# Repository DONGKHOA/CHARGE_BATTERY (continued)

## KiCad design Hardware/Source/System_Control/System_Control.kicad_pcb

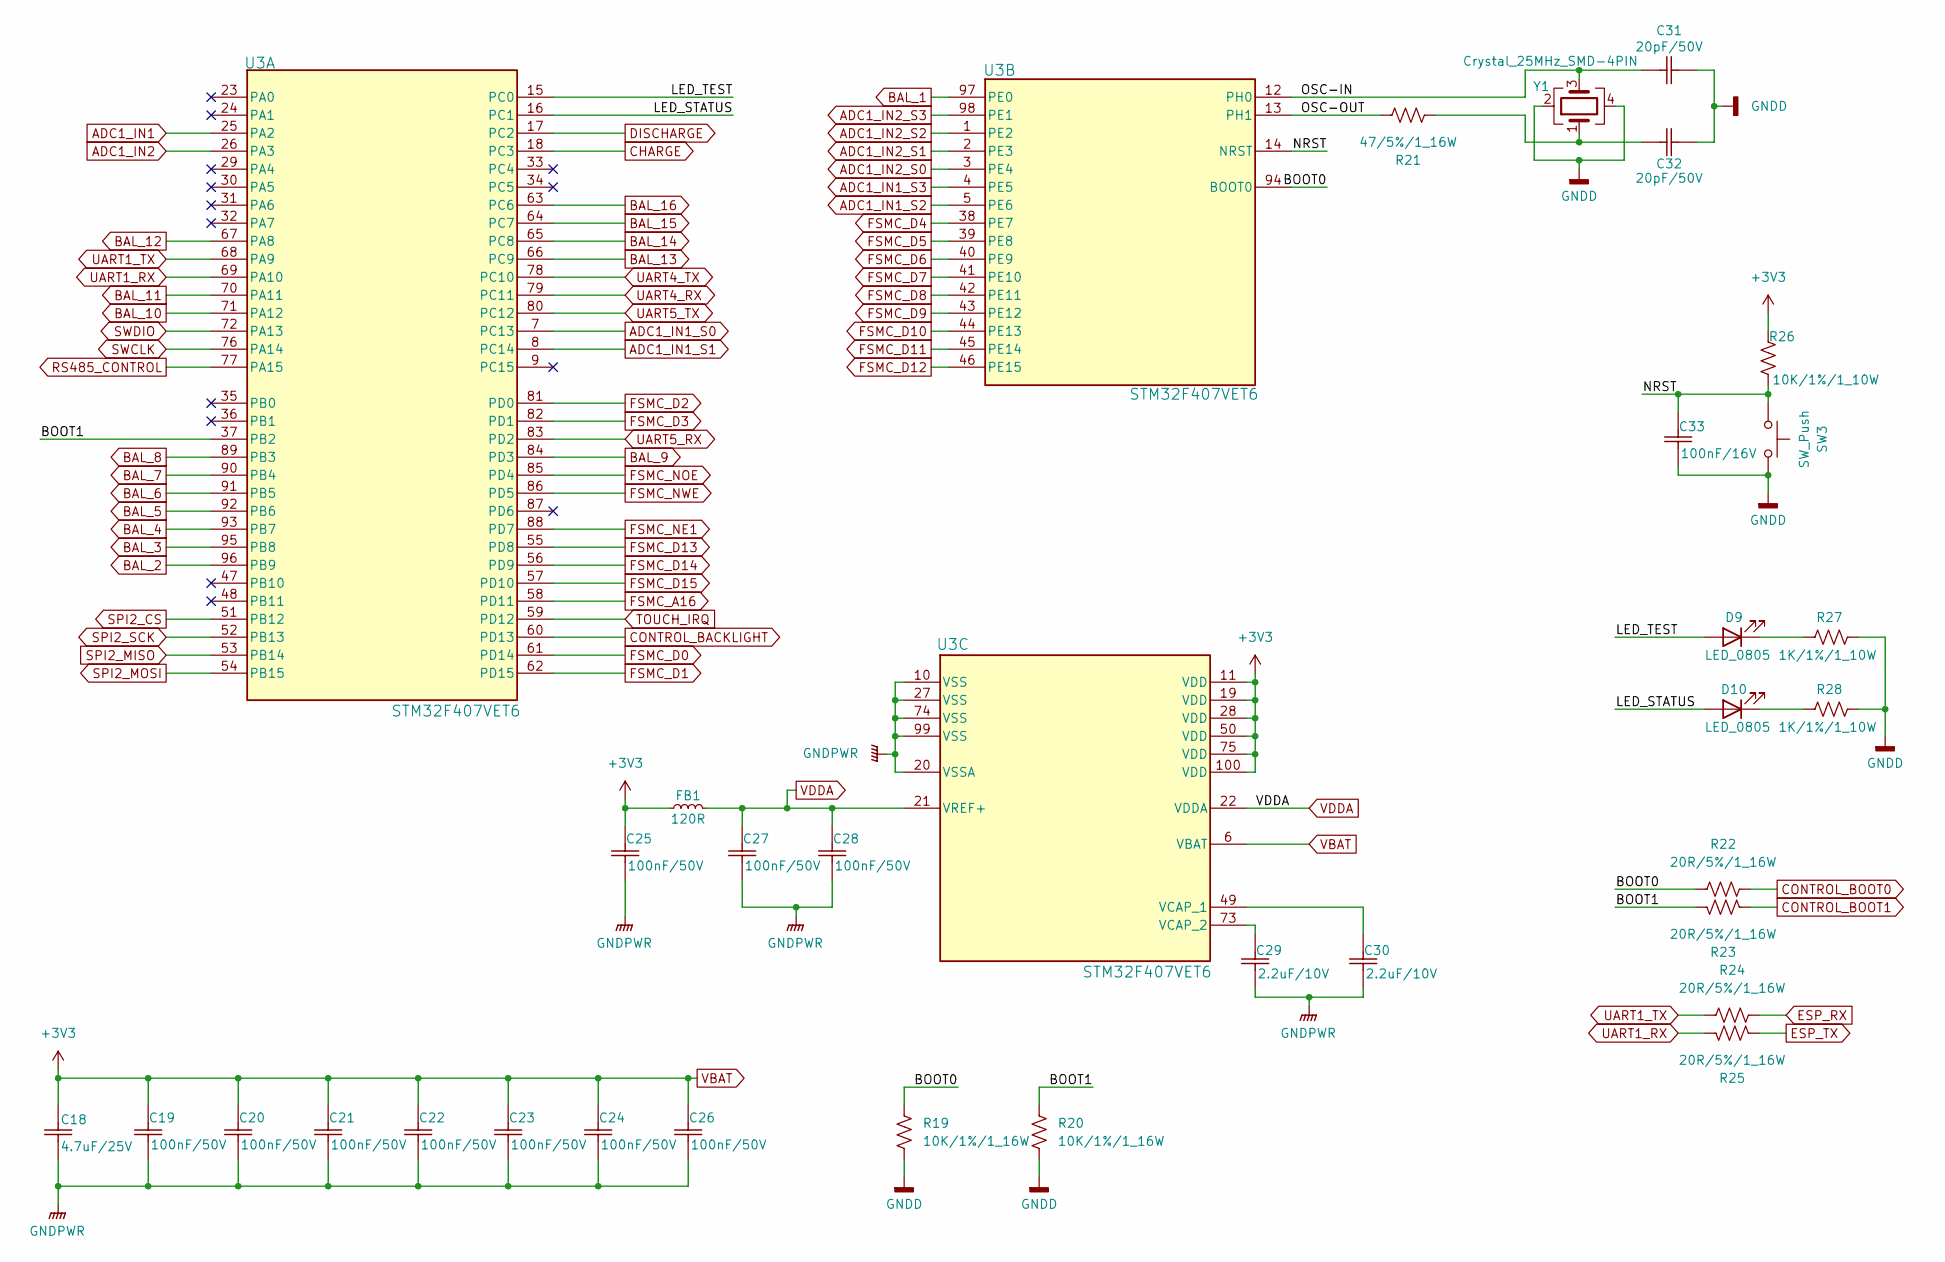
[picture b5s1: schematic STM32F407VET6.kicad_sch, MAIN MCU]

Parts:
C18: 4.7uF/25V; Ceramic_Cap_0603
C19, C20, C21, C22, C23, C24, C25, C26, C27, C28: 100nF/50V; Ceramic_Cap_0402
C29, C30: 2.2uF/10V; Ceramic_Cap_0603
C31, C32: 20pF/50V; Ceramic_Cap_0603
C33: 100nF/16V; Ceramic_Cap_0603
D9, D10: LED_0805
FB1: 120R; L_0805_2012Metric
R19, R20: 10K/1%/1_16W; Res_0402
R21: 47/5%/1_16W; Res_0402
R22, R23, R24, R25: 20R/5%/1_16W; Res_0402
R26: 10K/1%/1_10W; Res_0603
R27, R28: 1K/1%/1_10W; Res_0603
SW3: SW_Push; SW_SMD
U3: STM32F407VET6
Y1: Crystal_25MHz_SMD-4PIN; Crystal_SMD_4PIN_3225

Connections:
/STM32F407VET6/BOOT0: R19.2, R22.1, U3.94 (BOOT0)
/STM32F407VET6/BOOT1: R20.2, R23.1, U3.37 (PB2)
/STM32F407VET6/LED_STATUS: D10.2 (A), U3.16 (PC1)
/STM32F407VET6/LED_TEST: D9.2 (A), U3.15 (PC0)
/STM32F407VET6/NRST: C33.2, R26.1, SW3.2, U3.14 (NRST)
/STM32F407VET6/OSC-IN: C31.1, U3.12 (PH0), Y1.3
/STM32F407VET6/OSC-OUT: R21.1, U3.13 (PH1)
ADC1_IN1: U3.25 (PA2); also elsewhere on the board
ADC1_IN1_S0: U3.7 (PC13); also elsewhere on the board
ADC1_IN1_S1: U3.8 (PC14); also elsewhere on the board
ADC1_IN1_S2: U3.5 (PE6); also elsewhere on the board
ADC1_IN1_S3: U3.4 (PE5); also elsewhere on the board
ADC1_IN2: U3.26 (PA3); also elsewhere on the board
ADC1_IN2_S0: U3.3 (PE4); also elsewhere on the board
ADC1_IN2_S1: U3.2 (PE3); also elsewhere on the board
ADC1_IN2_S2: U3.1 (PE2); also elsewhere on the board
ADC1_IN2_S3: U3.98 (PE1); also elsewhere on the board
BAL_1: U3.97 (PE0); also elsewhere on the board
BAL_2: U3.96 (PB9); also elsewhere on the board
BAL_3: U3.95 (PB8); also elsewhere on the board
BAL_4: U3.93 (PB7); also elsewhere on the board
BAL_5: U3.92 (PB6); also elsewhere on the board
BAL_6: U3.91 (PB5); also elsewhere on the board
BAL_7: U3.90 (PB4); also elsewhere on the board
BAL_8: U3.89 (PB3); also elsewhere on the board
BAL_9: U3.84 (PD3); also elsewhere on the board
BAL_10: U3.71 (PA12); also elsewhere on the board
BAL_11: U3.70 (PA11); also elsewhere on the board
BAL_13: U3.66 (PC9); also elsewhere on the board
BAL_14: U3.65 (PC8); also elsewhere on the board
BAL_15: U3.64 (PC7); also elsewhere on the board
BAL_16: U3.63 (PC6); also elsewhere on the board
CHARGE: U3.18 (PC3); also elsewhere on the board
CONTROL_BACKLIGHT: U3.60 (PD13); also elsewhere on the board
CONTROL_BOOT0: R22.2; also elsewhere on the board
CONTROL_BOOT1: R23.2; also elsewhere on the board
DISCHARGE: U3.17 (PC2); also elsewhere on the board
ESP_RX: R24.2; also elsewhere on the board
ESP_TX: R25.2; also elsewhere on the board
FSMC_A16: U3.58 (PD11); also elsewhere on the board
FSMC_D0: U3.61 (PD14); also elsewhere on the board
FSMC_D1: U3.62 (PD15); also elsewhere on the board
FSMC_D2: U3.81 (PD0); also elsewhere on the board
FSMC_D3: U3.82 (PD1); also elsewhere on the board
FSMC_D4: U3.38 (PE7); also elsewhere on the board
FSMC_D5: U3.39 (PE8); also elsewhere on the board
FSMC_D6: U3.40 (PE9); also elsewhere on the board
FSMC_D7: U3.41 (PE10); also elsewhere on the board
FSMC_D8: U3.42 (PE11); also elsewhere on the board
FSMC_D9: U3.43 (PE12); also elsewhere on the board
FSMC_D10: U3.44 (PE13); also elsewhere on the board
FSMC_D11: U3.45 (PE14); also elsewhere on the board
FSMC_D12: U3.46 (PE15); also elsewhere on the board
FSMC_D13: U3.55 (PD8); also elsewhere on the board
FSMC_D14: U3.56 (PD9); also elsewhere on the board
FSMC_D15: U3.57 (PD10); also elsewhere on the board
FSMC_NE1: U3.88 (PD7); also elsewhere on the board
FSMC_NOE: U3.85 (PD4); also elsewhere on the board
FSMC_NWE: U3.86 (PD5); also elsewhere on the board
FSMC_RESET: U3.87 (PD6); also elsewhere on the board
GNDA: C18.1, C19.1, C20.1, C21.1, C22.1, C23.1, C24.1, C25.1, C26.1, C27.1, C28.1, C29.1, C30.1, C31.2, C32.2, C33.1, R19.1, R20.1, R27.2, R28.2, SW3.1, U3.10 (VSS), U3.20 (VSSA), U3.27 (VSS), U3.74 (VSS), U3.99 (VSS), Y1.2, Y1.4; also elsewhere on the board
unnamed: C32.1, R21.2, Y1.1
unnamed: D9.1 (K), R27.1
unnamed: D10.1 (K), R28.1
unnamed: C30.2, U3.49 (VCAP_1)
unnamed: C29.2, U3.73 (VCAP_2)
RS485_CONTROL: U3.77 (PA15); also elsewhere on the board
SPI2_CS: U3.51 (PB12); also elsewhere on the board
SPI2_MISO: U3.53 (PB14); also elsewhere on the board
SPI2_MOSI: U3.54 (PB15); also elsewhere on the board
SPI2_SCK: U3.52 (PB13); also elsewhere on the board
SWCLK: U3.76 (PA14); also elsewhere on the board
SWDIO: U3.72 (PA13); also elsewhere on the board
TOUCH_IRQ: U3.59 (PD12); also elsewhere on the board
UART4_RX: U3.79 (PC11); also elsewhere on the board
UART4_TX: U3.78 (PC10); also elsewhere on the board
UART5_RX: U3.83 (PD2); also elsewhere on the board
UART5_TX: U3.80 (PC12); also elsewhere on the board
VBAT: C18.2, C19.2, C20.2, C21.2, C22.2, C23.2, C24.2, C25.2, C26.2, FB1.1, R26.2, U3.6 (VBAT), U3.11 (VDD), U3.19 (VDD), U3.28 (VDD), U3.50 (VDD), U3.75 (VDD), U3.100 (VDD); also elsewhere on the board
VDDA: C27.2, C28.2, FB1.2, U3.21 (VREF+), U3.22 (VDDA)

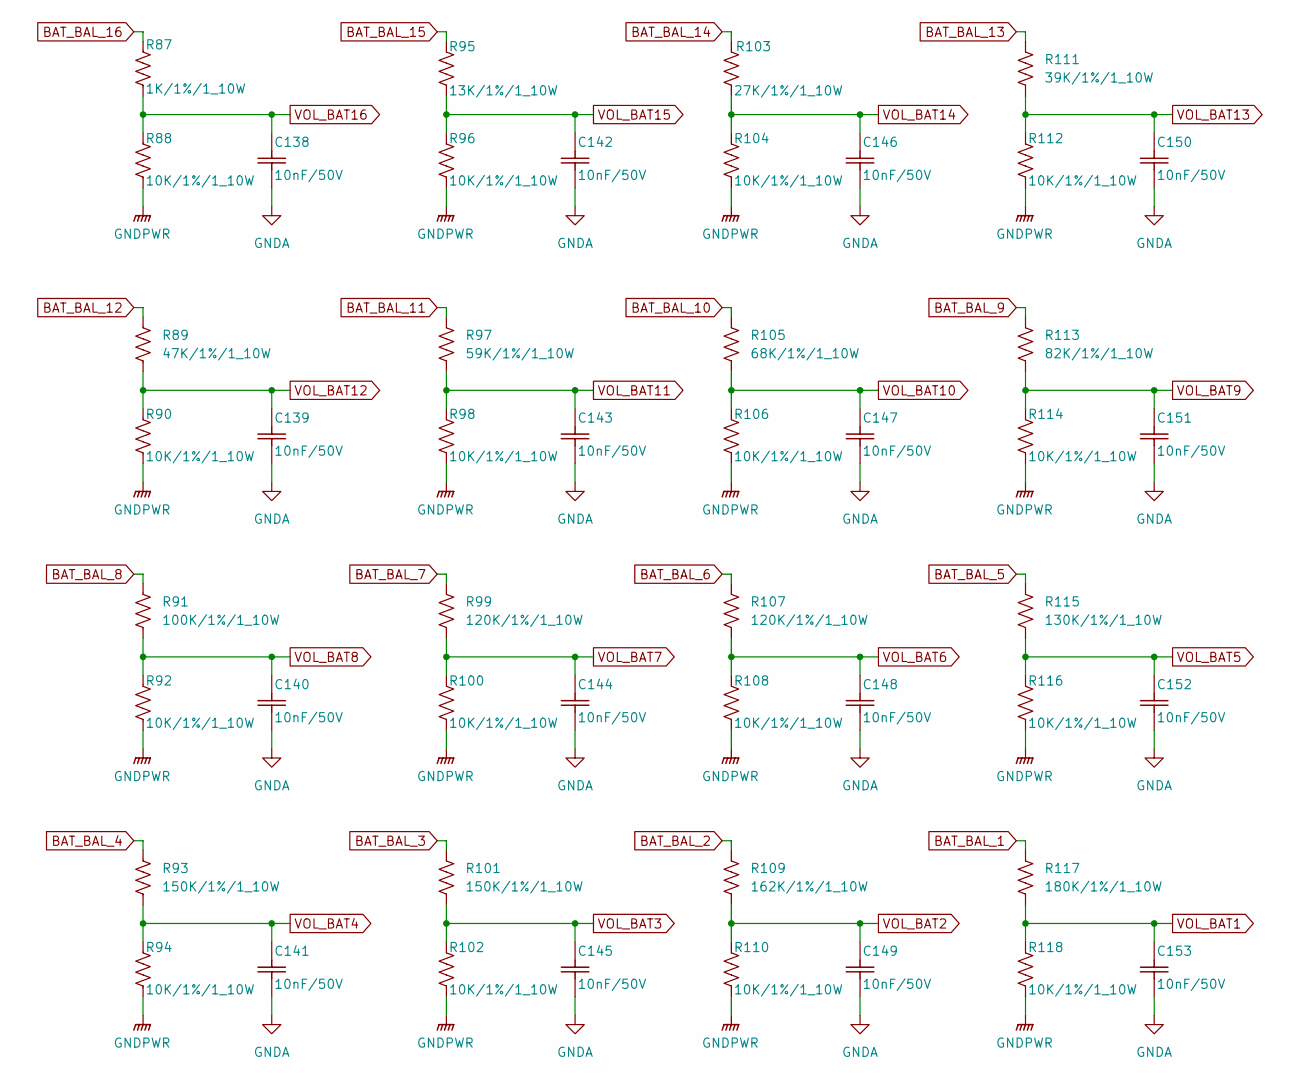
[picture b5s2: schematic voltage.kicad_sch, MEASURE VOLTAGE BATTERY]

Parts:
C138, C139, C140, C141, C142, C143, C144, C145, C146, C147, C148, C149, C150, C151, C152, C153: 10nF/50V; Ceramic_Cap_0603
R87: 1K/1%/1_10W; Res_0603
R88, R90, R92, R94, R96, R98, R100, R102, R104, R106, R108, R110, R112, R114, R116, R118: 10K/1%/1_10W; Res_0603
R89: 47K/1%/1_10W; Res_0603
R91: 100K/1%/1_10W; Res_0603
R93, R101: 150K/1%/1_10W; Res_0603
R95: 13K/1%/1_10W; Res_0603
R97: 59K/1%/1_10W; Res_0603
R99, R107: 120K/1%/1_10W; Res_0603
R103: 27K/1%/1_10W; Res_0603
R105: 68K/1%/1_10W; Res_0603
R109: 162K/1%/1_10W; Res_0603
R111: 39K/1%/1_10W; Res_0603
R113: 82K/1%/1_10W; Res_0603
R115: 130K/1%/1_10W; Res_0603
R117: 180K/1%/1_10W; Res_0603

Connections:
BAT_BAL_1: R117.2; also elsewhere on the board
BAT_BAL_2: R109.2; also elsewhere on the board
BAT_BAL_3: R101.2; also elsewhere on the board
BAT_BAL_4: R93.2; also elsewhere on the board
BAT_BAL_5: R115.2; also elsewhere on the board
BAT_BAL_6: R107.2; also elsewhere on the board
BAT_BAL_7: R99.2; also elsewhere on the board
BAT_BAL_8: R91.2; also elsewhere on the board
BAT_BAL_9: R113.2; also elsewhere on the board
BAT_BAL_10: R105.2; also elsewhere on the board
BAT_BAL_11: R97.2; also elsewhere on the board
BAT_BAL_12: R89.2; also elsewhere on the board
BAT_BAL_13: R111.2; also elsewhere on the board
BAT_BAL_14: R103.2; also elsewhere on the board
BAT_BAL_15: R95.1; also elsewhere on the board
BAT_BAL_16: R87.2; also elsewhere on the board
GNDA: C138.1, C139.1, C140.1, C141.1, C142.1, C143.1, C144.1, C145.1, C146.1, C147.1, C148.1, C149.1, C150.1, C151.1, C152.1, C153.1, R88.1, R90.1, R92.1, R94.1, R96.1, R98.1, R100.1, R102.1, R104.1, R106.1, R108.1, R110.1, R112.1, R114.1, R116.1, R118.1; also elsewhere on the board
VOL_BAT1: C153.2, R117.1, R118.2; also elsewhere on the board
VOL_BAT2: C149.2, R109.1, R110.2; also elsewhere on the board
VOL_BAT3: C145.2, R101.1, R102.2; also elsewhere on the board
VOL_BAT4: C141.2, R93.1, R94.2; also elsewhere on the board
VOL_BAT5: C152.2, R115.1, R116.2; also elsewhere on the board
VOL_BAT6: C148.2, R107.1, R108.2; also elsewhere on the board
VOL_BAT7: C144.2, R99.1, R100.2; also elsewhere on the board
VOL_BAT8: C140.2, R91.1, R92.2; also elsewhere on the board
VOL_BAT9: C151.2, R113.1, R114.2; also elsewhere on the board
VOL_BAT10: C147.2, R105.1, R106.2; also elsewhere on the board
VOL_BAT11: C143.2, R97.1, R98.2; also elsewhere on the board
VOL_BAT12: C139.2, R89.1, R90.2; also elsewhere on the board
VOL_BAT13: C150.2, R111.1, R112.2; also elsewhere on the board
VOL_BAT14: C146.2, R103.1, R104.2; also elsewhere on the board
VOL_BAT15: C142.2, R95.2, R96.2; also elsewhere on the board
VOL_BAT16: C138.2, R87.1, R88.2; also elsewhere on the board

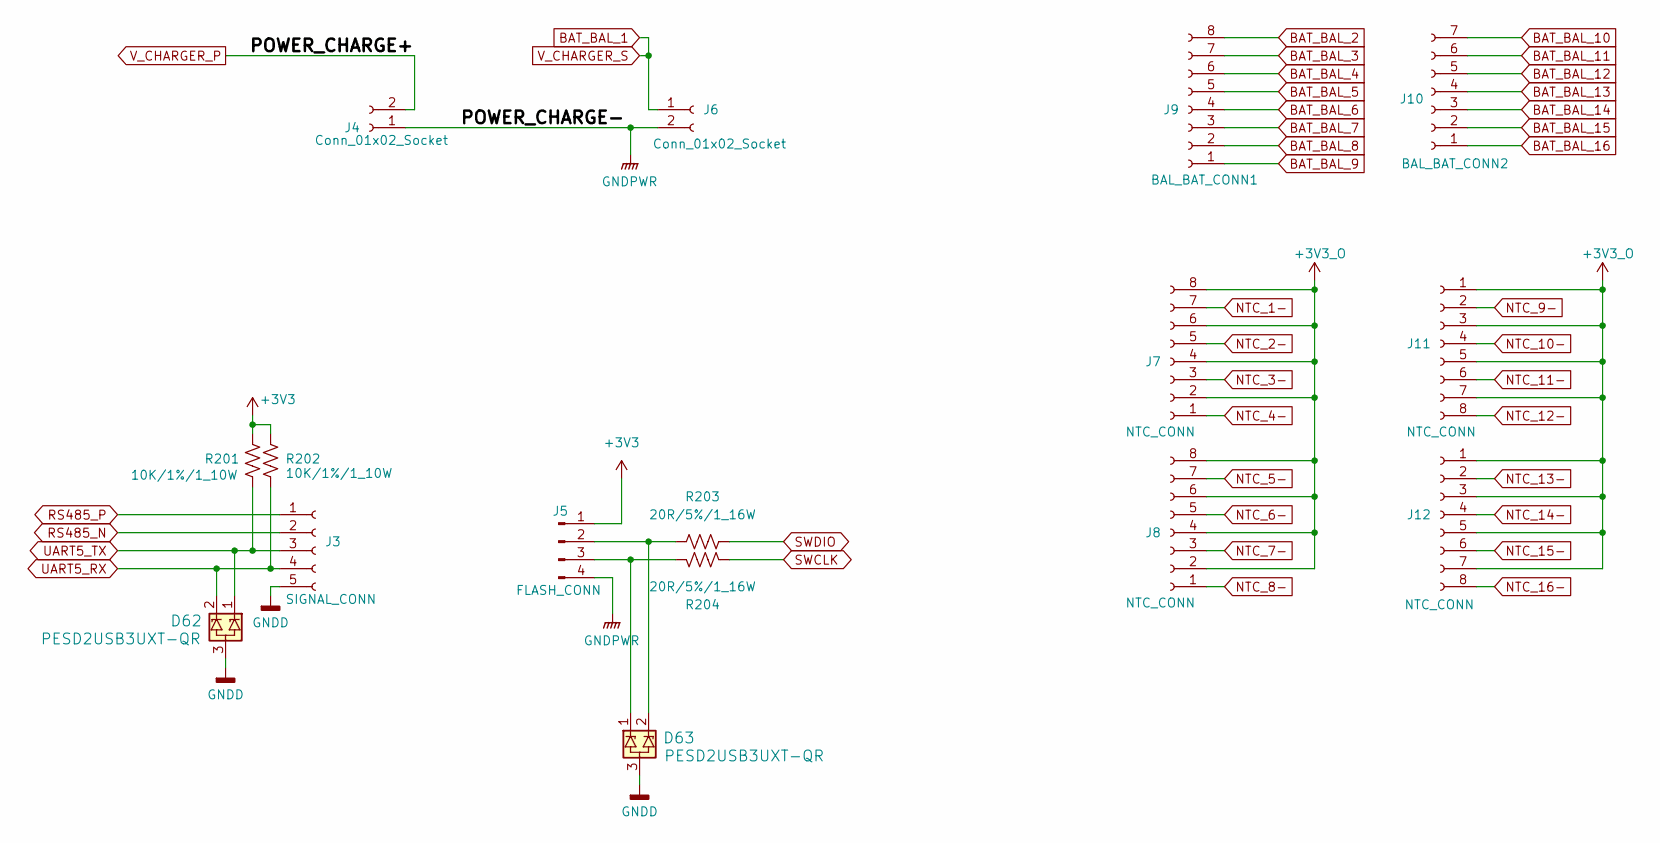
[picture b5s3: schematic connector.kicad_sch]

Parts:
D62, D63: PESD2USB3UXT-QR; SOT23
J3: SIGNAL_CONN; PhoenixContact_MC_1,5_5-G-3.81_1x05_P3.81mm_Horizontal
J4, J6: Conn_01x02_Socket; PhoenixContact_MC_1,5_2-G-3.81_1x02_P3.81mm_Horizontal
J5: FLASH_CONN; PinHeader_1x04_P2.54mm_Vertical
J7, J8, J11, J12: NTC_CONN; XH_2.54mm_8_SMD
J9: BAL_BAT_CONN1; PhoenixContact_MC_1,5_8-G-3.81_1x08_P3.81mm_Horizontal
J10: BAL_BAT_CONN2; PhoenixContact_MC_1,5_7-G-3.81_1x07_P3.81mm_Horizontal
R201, R202: 10K/1%/1_10W; Res_0603
R203, R204: 20R/5%/1_16W; Res_0402

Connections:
+3V3_O: J7.2, J7.4, J7.6, J7.8, J8.2, J8.4, J8.6, J8.8, J11.1, J11.3, J11.5, J11.7, J12.1, J12.3, J12.5, J12.7; also elsewhere on the board
BAT_BAL_1: J6.1; also elsewhere on the board
BAT_BAL_2: J9.8; also elsewhere on the board
BAT_BAL_3: J9.7; also elsewhere on the board
BAT_BAL_4: J9.6; also elsewhere on the board
BAT_BAL_5: J9.5; also elsewhere on the board
BAT_BAL_6: J9.4; also elsewhere on the board
BAT_BAL_7: J9.3; also elsewhere on the board
BAT_BAL_8: J9.2; also elsewhere on the board
BAT_BAL_9: J9.1; also elsewhere on the board
BAT_BAL_10: J10.7; also elsewhere on the board
BAT_BAL_11: J10.6; also elsewhere on the board
BAT_BAL_12: J10.5; also elsewhere on the board
BAT_BAL_13: J10.4; also elsewhere on the board
BAT_BAL_14: J10.3; also elsewhere on the board
BAT_BAL_15: J10.2; also elsewhere on the board
BAT_BAL_16: J10.1; also elsewhere on the board
GNDA: D62.3, D63.3, J3.5, J4.1, J5.4, J6.2; also elsewhere on the board
NTC_1-: J7.7; also elsewhere on the board
NTC_2-: J7.5; also elsewhere on the board
NTC_3-: J7.3; also elsewhere on the board
NTC_4-: J7.1; also elsewhere on the board
NTC_5-: J8.7; also elsewhere on the board
NTC_6-: J8.5; also elsewhere on the board
NTC_7-: J8.3; also elsewhere on the board
NTC_8-: J8.1; also elsewhere on the board
NTC_9-: J11.2; also elsewhere on the board
NTC_10-: J11.4; also elsewhere on the board
NTC_11-: J11.6; also elsewhere on the board
NTC_12-: J11.8; also elsewhere on the board
NTC_13-: J12.2; also elsewhere on the board
NTC_14-: J12.4; also elsewhere on the board
NTC_15-: J12.6; also elsewhere on the board
NTC_16-: J12.8; also elsewhere on the board
unnamed: D63.2, J5.2, R203.1
unnamed: D63.1, J5.3, R204.1
RS485_N: J3.2; also elsewhere on the board
RS485_P: J3.1; also elsewhere on the board
SWCLK: R204.2; also elsewhere on the board
SWDIO: R203.2; also elsewhere on the board
UART5_RX: D62.2, J3.4, R202.1; also elsewhere on the board
UART5_TX: D62.1, J3.3, R201.1; also elsewhere on the board
VBAT: J5.1, R201.2, R202.2; also elsewhere on the board
V_CHARGER_P: J4.2; also elsewhere on the board

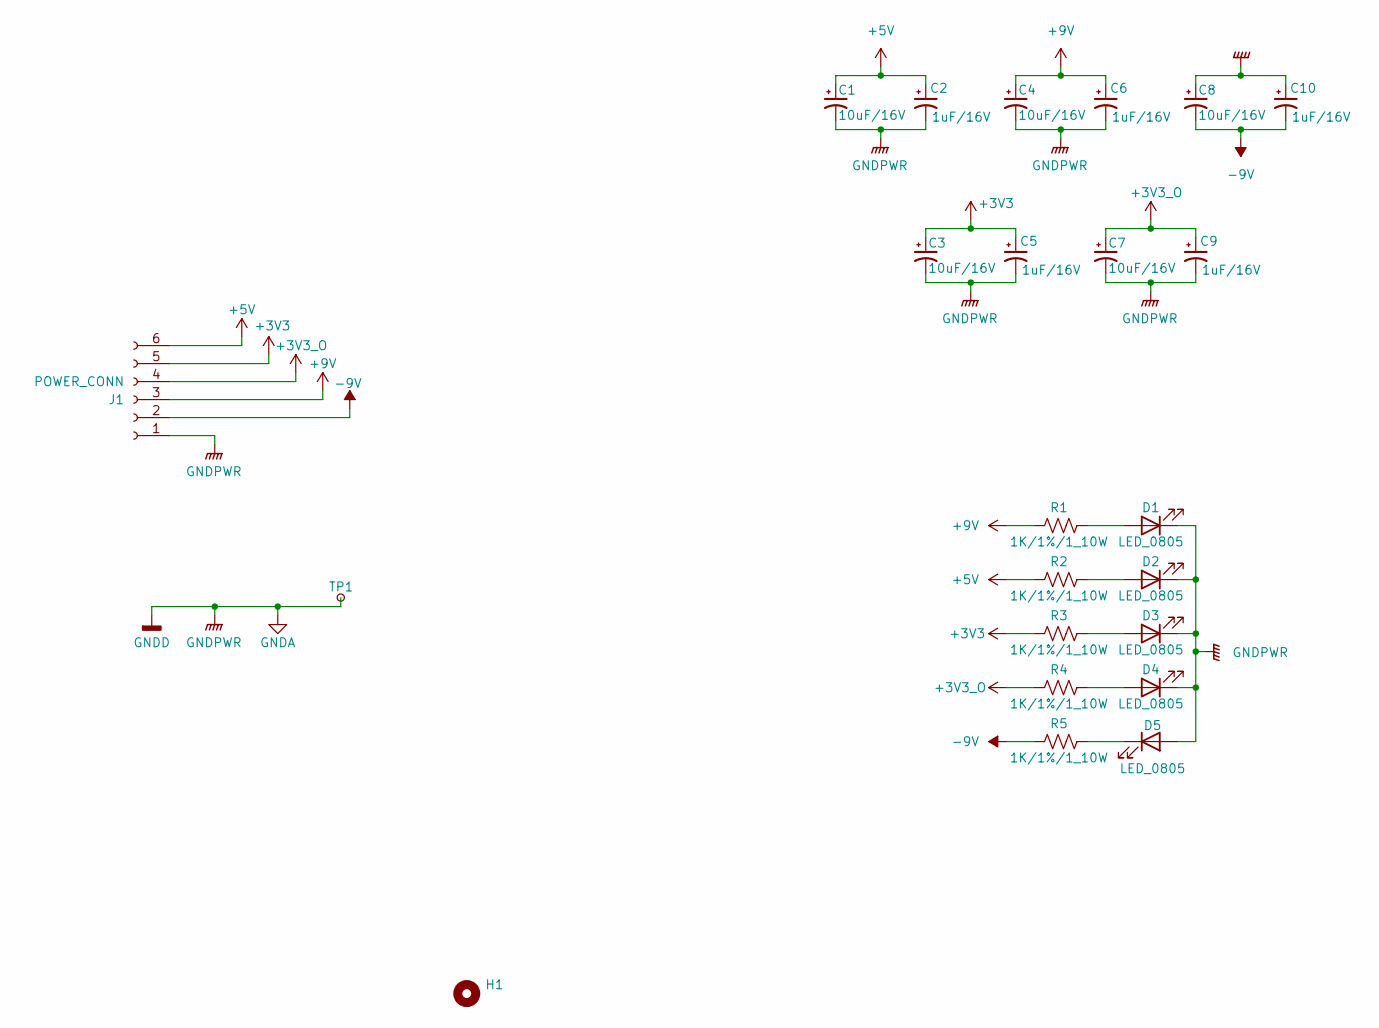
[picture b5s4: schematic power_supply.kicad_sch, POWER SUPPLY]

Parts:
C1, C3, C4, C7, C8: 10uF/16V; Tan_Cap_A
C2, C5, C6, C9, C10: 1uF/16V; Tan_Cap_A
D1, D2, D3, D4, D5: LED_0805
H1: MountingHole; MountingHole_3.2mm_M3_ISO7380_Pad_TopBottom
J1: POWER_CONN; PhoenixContact_MC_1,5_6-G-3.81_1x06_P3.81mm_Horizontal
R1, R2, R3, R4, R5: 1K/1%/1_10W; Res_0603
TP1: GND; TestPoint_Pad_D1.0mm

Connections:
+3V3_O: C7.1, C9.1, J1.4, R4.1; also elsewhere on the board
+5V: C1.1, C2.1, J1.6, R2.1; also elsewhere on the board
+9V: C4.1, C6.1, J1.3, R1.1; also elsewhere on the board
-9V: C8.2, C10.2, J1.2, R5.1; also elsewhere on the board
GNDA: C1.2, C2.2, C3.2, C4.2, C5.2, C6.2, C7.2, C8.1, C9.2, C10.1, D1.1 (K), D2.1 (K), D3.1 (K), D4.1 (K), D5.2 (A), J1.1, TP1.1; also elsewhere on the board
unnamed: D1.2 (A), R1.2
unnamed: D2.2 (A), R2.2
unnamed: D3.2 (A), R3.2
unnamed: D4.2 (A), R4.2
unnamed: D5.1 (K), R5.2
VBAT: C3.1, C5.1, J1.5, R3.1; also elsewhere on the board

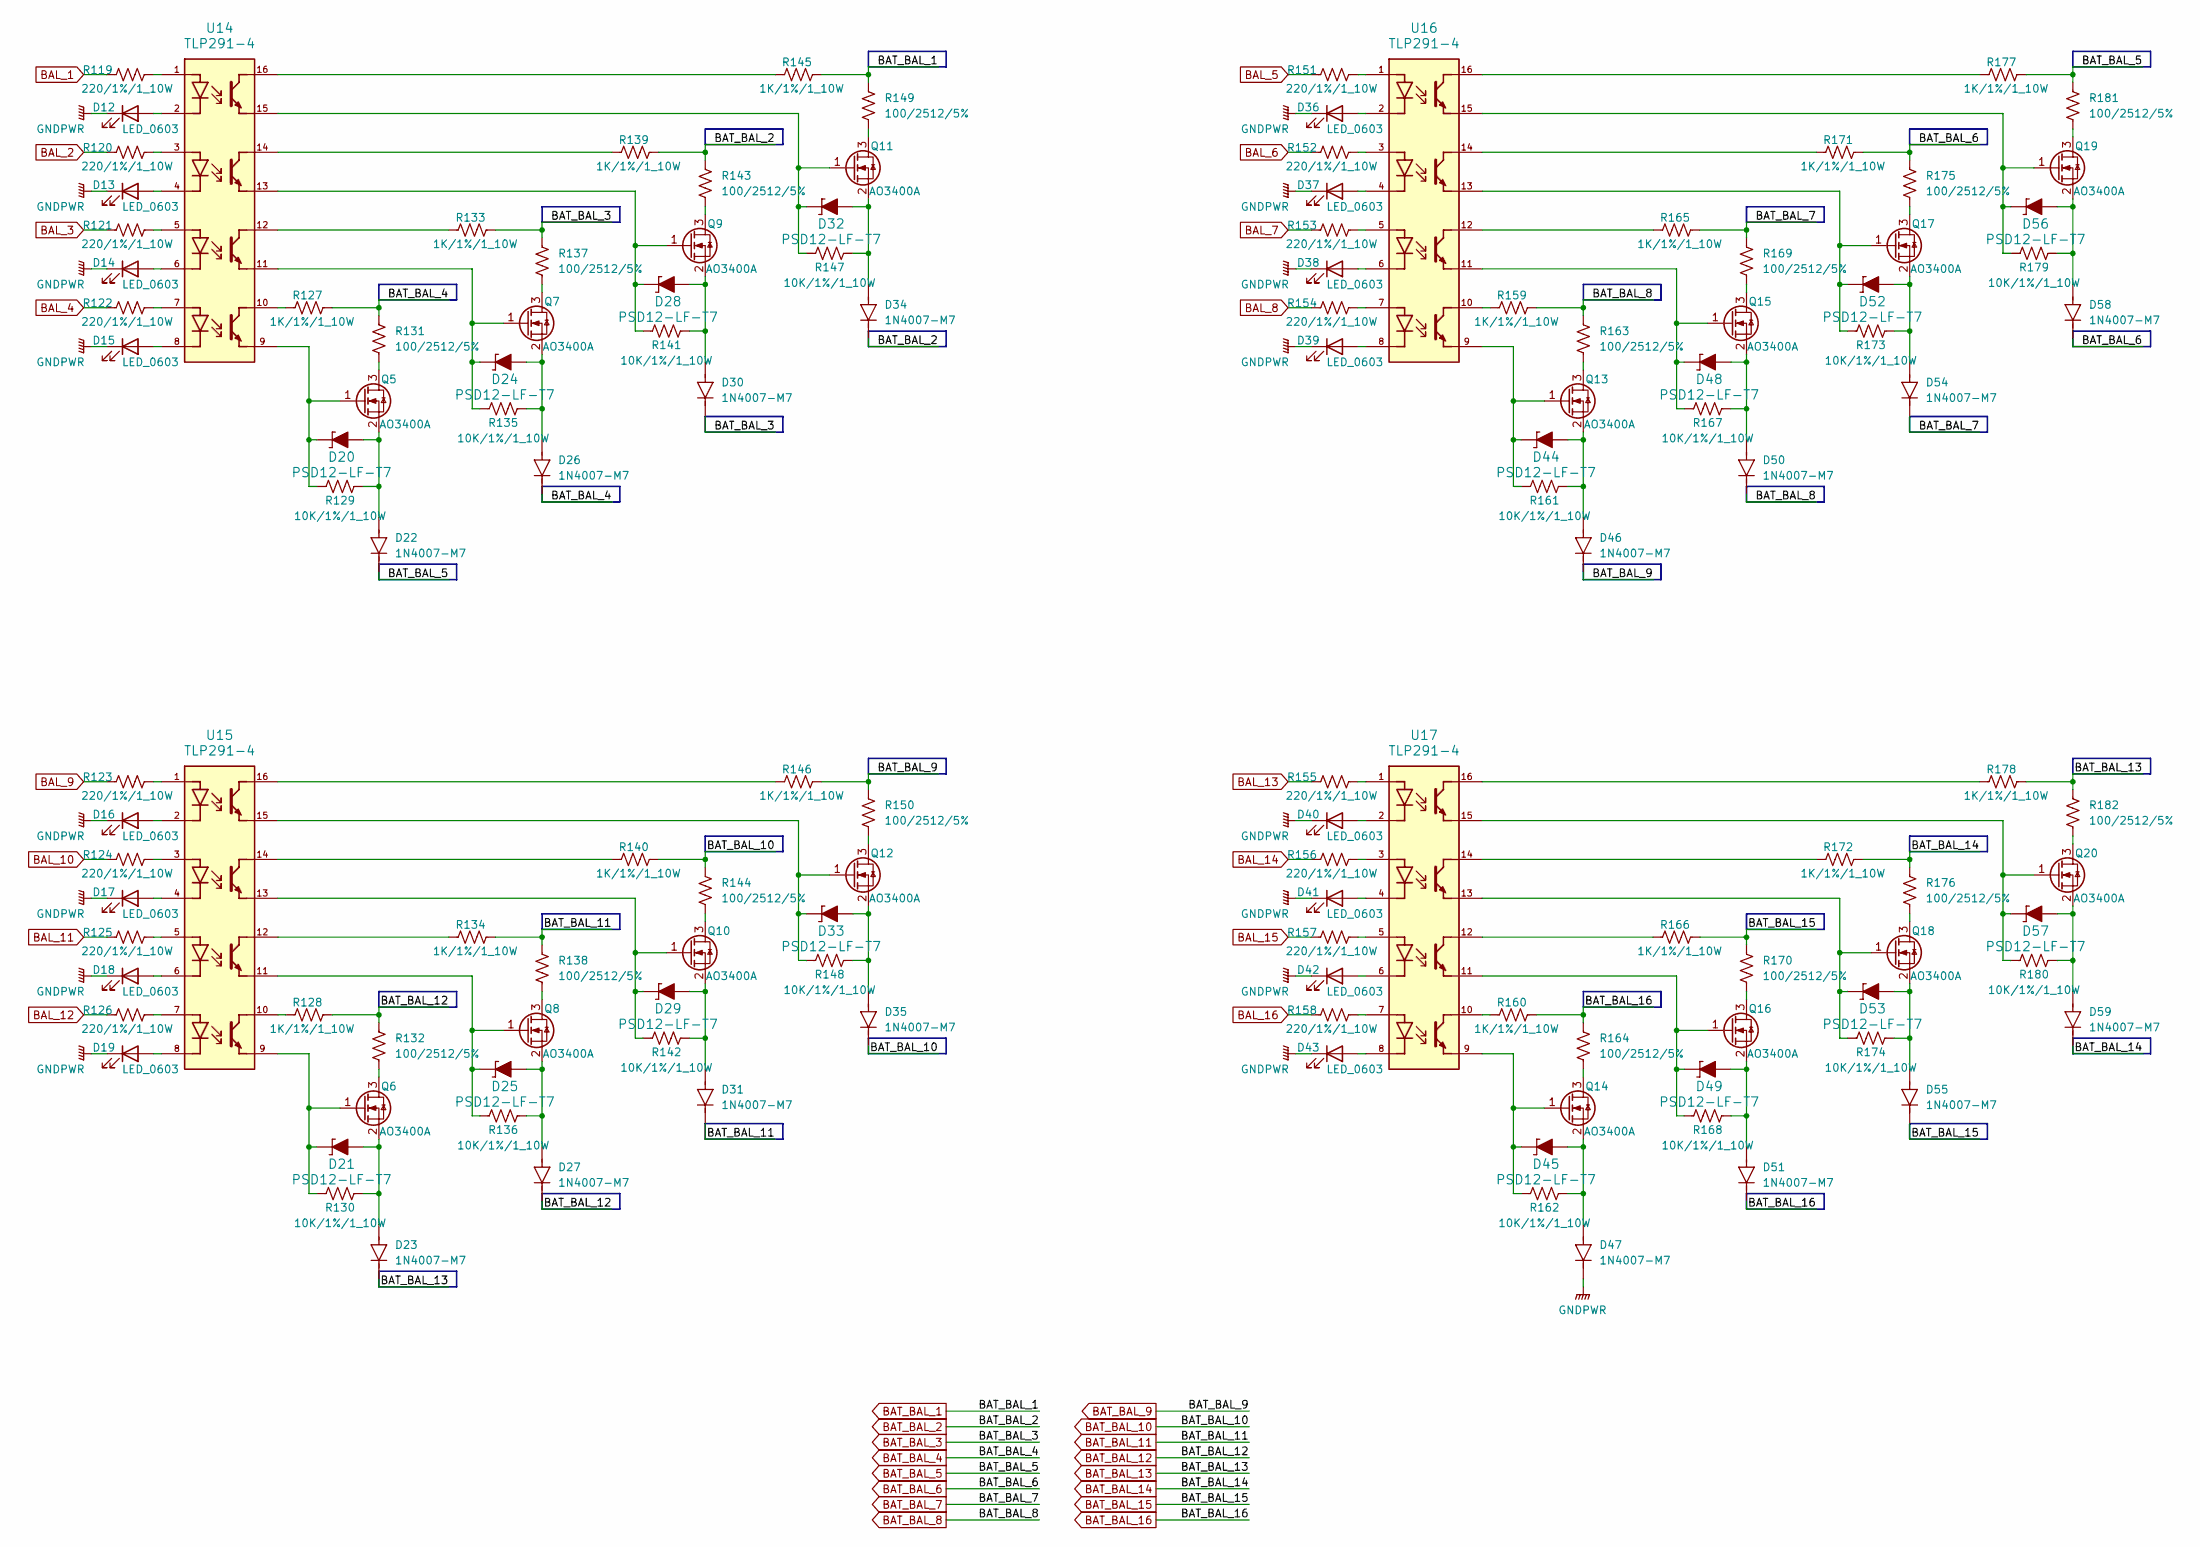
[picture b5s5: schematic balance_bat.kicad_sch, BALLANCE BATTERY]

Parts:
D12, D13, D14, D15, D16, D17, D18, D19, D36, D37, D38, D39, D40, D41, D42, D43: LED_0603
D20, D21, D24, D25, D28, D29, D32, D33, D44, D45, D48, D49, D52, D53, D56, D57: PSD12-LF-T7; SOD-323_PTD
D22, D23, D26, D27, D30, D31, D34, D35, D46, D47, D50, D51, D54, D55, D58, D59: 1N4007-M7; D_SMA
Q5, Q6, Q7, Q8, Q9, Q10, Q11, Q12, Q13, Q14, Q15, Q16, Q17, Q18, Q19, Q20: AO3400A; SOT23
R119, R120, R121, R122, R123, R124, R125, R126, R151, R152, R153, R154, R155, R156, R157, R158: 220/1%/1_10W; Res_0603
R127, R128, R133, R134, R139, R140, R145, R146, R159, R160, R165, R166, R171, R172, R177, R178: 1K/1%/1_10W; Res_0603
R129, R130, R135, R136, R141, R142, R147, R148, R161, R162, R167, R168, R173, R174, R179, R180: 10K/1%/1_10W; Res_0603
R131, R132, R137, R138, R143, R144, R149, R150, R163, R164, R169, R170, R175, R176, R181, R182: 100/2512/5%; Res_2512
U14, U15, U16, U17: TLP291-4; SOIC-16

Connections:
BAL_1: R119.1; also elsewhere on the board
BAL_2: R120.1; also elsewhere on the board
BAL_3: R121.1; also elsewhere on the board
BAL_4: R122.1; also elsewhere on the board
BAL_5: R151.1; also elsewhere on the board
BAL_6: R152.1; also elsewhere on the board
BAL_7: R153.1; also elsewhere on the board
BAL_8: R154.1; also elsewhere on the board
BAL_9: R123.1; also elsewhere on the board
BAL_10: R124.1; also elsewhere on the board
BAL_11: R125.1; also elsewhere on the board
BAL_13: R155.1; also elsewhere on the board
BAL_14: R156.1; also elsewhere on the board
BAL_15: R157.1; also elsewhere on the board
BAL_16: R158.1; also elsewhere on the board
BAT_BAL_1: R145.2, R149.2; also elsewhere on the board
BAT_BAL_2: D34.2 (K), R139.2, R143.2; also elsewhere on the board
BAT_BAL_3: D30.2 (K), R133.2, R137.2; also elsewhere on the board
BAT_BAL_4: D26.2 (K), R127.2, R131.2; also elsewhere on the board
BAT_BAL_5: D22.2 (K), R177.2, R181.2; also elsewhere on the board
BAT_BAL_6: D58.2 (K), R171.2, R175.2; also elsewhere on the board
BAT_BAL_7: D54.2 (K), R165.2, R169.2; also elsewhere on the board
BAT_BAL_8: D50.2 (K), R159.2, R163.2; also elsewhere on the board
BAT_BAL_9: D46.2 (K), R146.2, R150.2; also elsewhere on the board
BAT_BAL_10: D35.2 (K), R140.2, R144.2; also elsewhere on the board
BAT_BAL_11: D31.2 (K), R134.2, R138.2; also elsewhere on the board
BAT_BAL_12: D27.2 (K), R128.2, R132.2; also elsewhere on the board
BAT_BAL_13: D23.2 (K), R178.2, R182.2; also elsewhere on the board
BAT_BAL_14: D59.2 (K), R172.2, R176.2; also elsewhere on the board
BAT_BAL_15: D55.2 (K), R166.2, R170.2; also elsewhere on the board
BAT_BAL_16: D51.2 (K), R160.2, R164.2; also elsewhere on the board
GNDA: D12.1 (K), D13.1 (K), D14.1 (K), D15.1 (K), D16.1 (K), D17.1 (K), D18.1 (K), D19.1 (K), D36.1 (K), D37.1 (K), D38.1 (K), D39.1 (K), D40.1 (K), D41.1 (K), D42.1 (K), D43.1 (K), D47.2 (K); also elsewhere on the board
unnamed: D12.2 (A), U14.2 (K)
unnamed: D13.2 (A), U14.4 (K)
unnamed: D14.2 (A), U14.6 (K)
unnamed: D15.2 (A), U14.8 (K)
unnamed: D16.2 (A), U15.2 (K)
unnamed: D17.2 (A), U15.4 (K)
unnamed: D18.2 (A), U15.6 (K)
unnamed: D19.2 (A), U15.8 (K)
unnamed: D20.2, D22.1 (A), Q5.2 (S), R129.2
unnamed: D21.2, D23.1 (A), Q6.2 (S), R130.2
unnamed: D24.2, D26.1 (A), Q7.2 (S), R135.2
unnamed: D25.2, D27.1 (A), Q8.2 (S), R136.2
unnamed: D28.2, D30.1 (A), Q9.2 (S), R141.2
unnamed: D29.2, D31.1 (A), Q10.2 (S), R142.2
unnamed: D32.2, D34.1 (A), Q11.2 (S), R147.2
unnamed: D33.2, D35.1 (A), Q12.2 (S), R148.2
unnamed: D36.2 (A), U16.2 (K)
unnamed: D37.2 (A), U16.4 (K)
unnamed: D38.2 (A), U16.6 (K)
unnamed: D39.2 (A), U16.8 (K)
unnamed: D40.2 (A), U17.2 (K)
unnamed: D41.2 (A), U17.4 (K)
unnamed: D42.2 (A), U17.6 (K)
unnamed: D43.2 (A), U17.8 (K)
unnamed: D44.2, D46.1 (A), Q13.2 (S), R161.2
unnamed: D45.2, D47.1 (A), Q14.2 (S), R162.2
unnamed: D48.2, D50.1 (A), Q15.2 (S), R167.2
unnamed: D49.2, D51.1 (A), Q16.2 (S), R168.2
unnamed: D52.2, D54.1 (A), Q17.2 (S), R173.2
unnamed: D53.2, D55.1 (A), Q18.2 (S), R174.2
unnamed: D56.2, D58.1 (A), Q19.2 (S), R179.2
unnamed: D57.2, D59.1 (A), Q20.2 (S), R180.2
unnamed: Q5.3 (D), R131.1
unnamed: D20.1, Q5.1 (G), R129.1, U14.9 (E)
unnamed: Q6.3 (D), R132.1
unnamed: D21.1, Q6.1 (G), R130.1, U15.9 (E)
unnamed: Q7.3 (D), R137.1
unnamed: D24.1, Q7.1 (G), R135.1, U14.11 (E)
unnamed: Q8.3 (D), R138.1
unnamed: D25.1, Q8.1 (G), R136.1, U15.11 (E)
unnamed: Q9.3 (D), R143.1
unnamed: D28.1, Q9.1 (G), R141.1, U14.13 (E)
unnamed: Q10.3 (D), R144.1
unnamed: D29.1, Q10.1 (G), R142.1, U15.13 (E)
unnamed: Q11.3 (D), R149.1
unnamed: D32.1, Q11.1 (G), R147.1, U14.15 (E)
unnamed: Q12.3 (D), R150.1
unnamed: D33.1, Q12.1 (G), R148.1, U15.15 (E)
unnamed: Q13.3 (D), R163.1
unnamed: D44.1, Q13.1 (G), R161.1, U16.9 (E)
unnamed: Q14.3 (D), R164.1
unnamed: D45.1, Q14.1 (G), R162.1, U17.9 (E)
unnamed: Q15.3 (D), R169.1
unnamed: D48.1, Q15.1 (G), R167.1, U16.11 (E)
unnamed: Q16.3 (D), R170.1
unnamed: D49.1, Q16.1 (G), R168.1, U17.11 (E)
unnamed: Q17.3 (D), R175.1
unnamed: D52.1, Q17.1 (G), R173.1, U16.13 (E)
unnamed: Q18.3 (D), R176.1
unnamed: D53.1, Q18.1 (G), R174.1, U17.13 (E)
unnamed: Q19.3 (D), R181.1
unnamed: D56.1, Q19.1 (G), R179.1, U16.15 (E)
unnamed: Q20.3 (D), R182.1
unnamed: D57.1, Q20.1 (G), R180.1, U17.15 (E)
unnamed: R119.2, U14.1 (A)
unnamed: R120.2, U14.3 (A)
unnamed: R121.2, U14.5 (A)
unnamed: R122.2, U14.7 (A)
unnamed: R123.2, U15.1 (A)
unnamed: R124.2, U15.3 (A)
unnamed: R125.2, U15.5 (A)
unnamed: R126.2, U15.7 (A)
unnamed: R127.1, U14.10 (C)
unnamed: R128.1, U15.10 (C)
unnamed: R133.1, U14.12 (C)
unnamed: R134.1, U15.12 (C)
unnamed: R139.1, U14.14 (C)
unnamed: R140.1, U15.14 (C)
unnamed: R145.1, U14.16 (C)
unnamed: R146.1, U15.16 (C)
unnamed: R151.2, U16.1 (A)
unnamed: R152.2, U16.3 (A)
unnamed: R153.2, U16.5 (A)
unnamed: R154.2, U16.7 (A)
unnamed: R155.2, U17.1 (A)
unnamed: R156.2, U17.3 (A)
unnamed: R157.2, U17.5 (A)
unnamed: R158.2, U17.7 (A)
unnamed: R159.1, U16.10 (C)
unnamed: R160.1, U17.10 (C)
unnamed: R165.1, U16.12 (C)
unnamed: R166.1, U17.12 (C)
unnamed: R171.1, U16.14 (C)
unnamed: R172.1, U17.14 (C)
unnamed: R177.1, U16.16 (C)
unnamed: R178.1, U17.16 (C)
